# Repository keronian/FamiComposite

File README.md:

# FamiComposite
A Famicom Composite bypass adapter

This is a basic Famicom Composite bypass adapter, inspired by other compact designs, using the basic video circuit from [NESDev](https://www.nesdev.org/wiki/PPU_pinout#Composite_Video_Output), but with an additional optional spot for another 100µF decoupling capacitor.

Pin 22 of the PPU is used as a +5V here, as the reset pin of the PPU is tied to +5V in this system.

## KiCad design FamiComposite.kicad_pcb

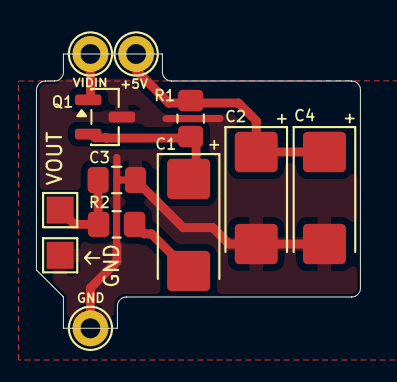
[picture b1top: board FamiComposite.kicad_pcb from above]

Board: 2 copper layers, 18.0 x 15.2 mm, 12 parts (0 on the bottom side), 6 nets.

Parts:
C1: 220uF; CP_EIA-6032-20_AVX-F_HandSolder
C2: 10uF; CP_EIA-6032-20_AVX-F_HandSolder
C3: 560pF; C_0805_2012Metric_Pad1.18x1.45mm_HandSolder
C4: 100uF; CP_EIA-6032-20_AVX-F_HandSolder
GND: GND; TestPoint_Pad_1.5x1.5mm
Q1: MMBT3906; SOT-23
R1: 300; R_0805_2012Metric_Pad1.20x1.40mm_HandSolder
R2: 110; R_0805_2012Metric_Pad1.20x1.40mm_HandSolder
TP1: VIDIN; TestPoint_THTPad_D2.0mm_Drill1.0mm
TP2: +5V; TestPoint_THTPad_D2.0mm_Drill1.0mm
TP3: GND; TestPoint_THTPad_D2.0mm_Drill1.0mm
VOUT: VIDEO; TestPoint_Pad_1.5x1.5mm

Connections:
+5V: C2.1, C4.1, R1.1, TP2.1 (1_1)
GND: C2.2, C3.1, C4.2, GND.1 (1_1), Q1.3 (C), TP3.1 (1_1)
unnamed: C1.2, R2.1
unnamed: C3.2, R2.2, VOUT.1 (1_1)
unnamed: Q1.1 (B), TP1.1 (1_1)
unnamed: C1.1, Q1.2 (E), R1.2

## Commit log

2026-06-12 Added first version
2026-06-12 Added render
2026-06-12 Fix image path
